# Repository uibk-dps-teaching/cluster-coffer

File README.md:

# Cluster Coffer

See [manual](docs/cluster-coffer.pdf).

See extra fancy [3D PDF](hardware/main-3d.pdf) that works only with Adobe Reader / Acrobat.

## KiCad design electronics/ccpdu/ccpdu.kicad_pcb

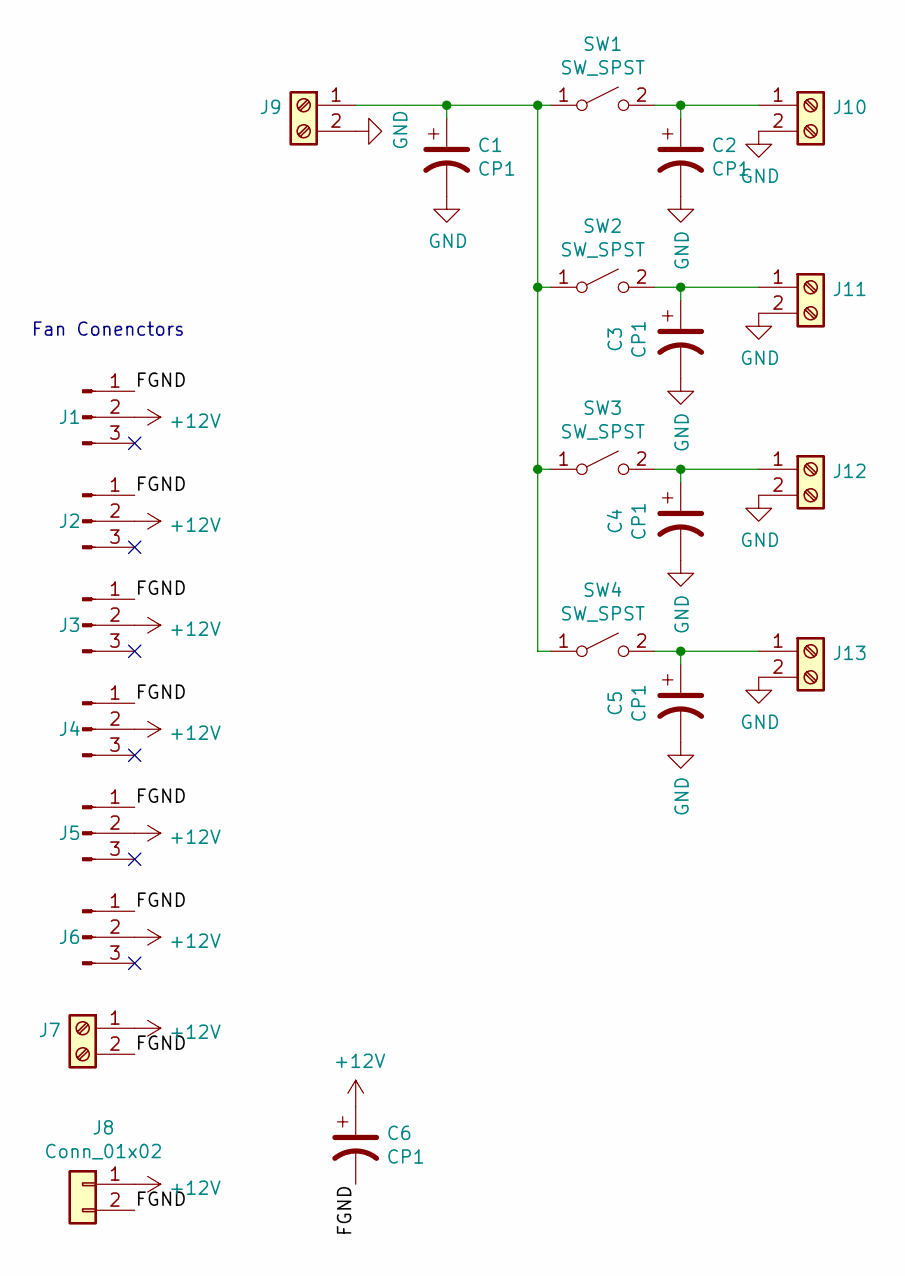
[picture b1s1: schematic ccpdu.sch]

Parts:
C1, C2, C3, C4, C5, C6: CP1; CP_Radial_D5.0mm_P2.50mm; DigikeyPN 493-12902-1-ND
J1, J2, J3, J4, J5, J6: Conn_01x03_Male; Molex_KK-254_AE-6410-03A_1x03_P2.54mm_Vertical; DigikeyPN WM2701-ND
J7, J9, J10, J11, J12, J13: Screw_Terminal_01x02; 284391-2; DigikeyPN A98159-ND
J8: Conn_01x02; HTLCONN_01x02
SW1, SW2, SW3, SW4: SW_SPST; RS-448-0747

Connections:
+12V: C6.1, J1.2, J2.2, J3.2, J4.2, J5.2, J6.2, J7.1, J8.1
/FGND: C6.2, J1.1, J2.1, J3.1, J4.1, J5.1, J6.1, J7.2, J8.2
GND: C1.2, C2.2, C3.2, C4.2, C5.2, J9.2, J10.2, J11.2, J12.2, J13.2
unnamed: C1.1, J9.1, SW1.1 (A), SW2.1 (A), SW3.1 (A), SW4.1 (A)
unnamed: C2.1, J10.1, SW1.2 (B)
unnamed: C3.1, J11.1, SW2.2 (B)
unnamed: C4.1, J12.1, SW3.2 (B)
unnamed: C5.1, J13.1, SW4.2 (B)

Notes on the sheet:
Fan Conenctors

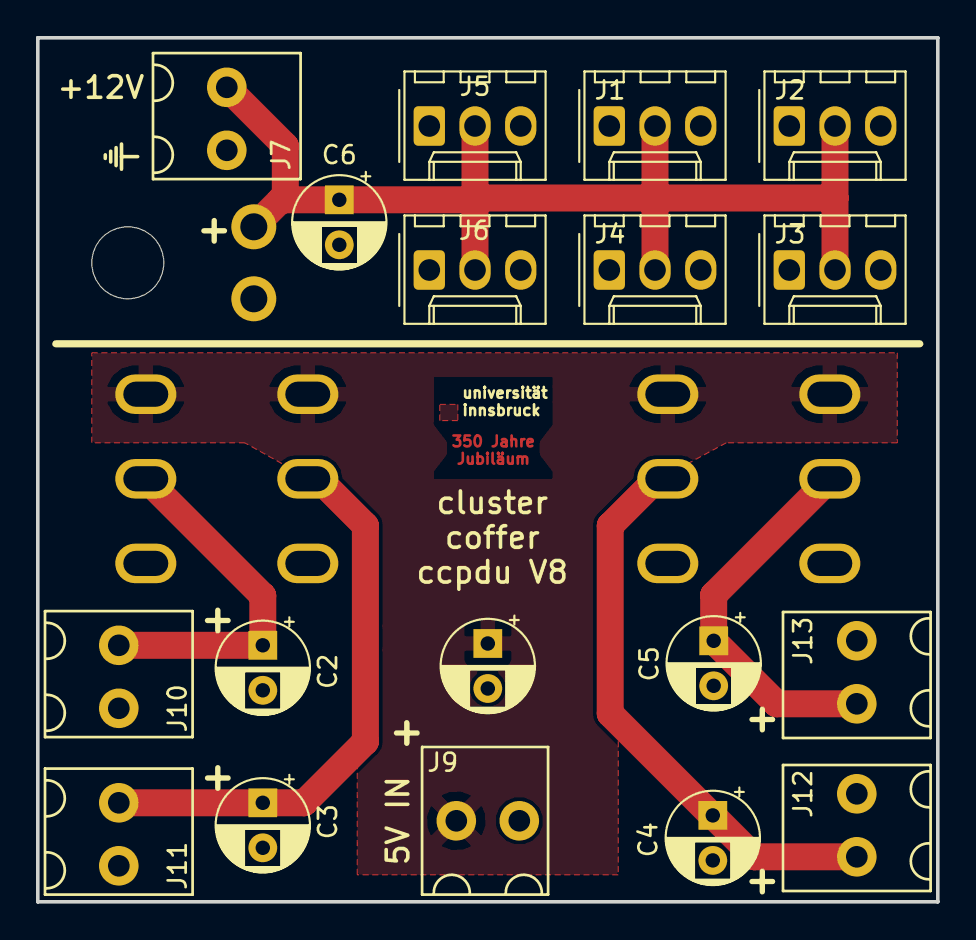
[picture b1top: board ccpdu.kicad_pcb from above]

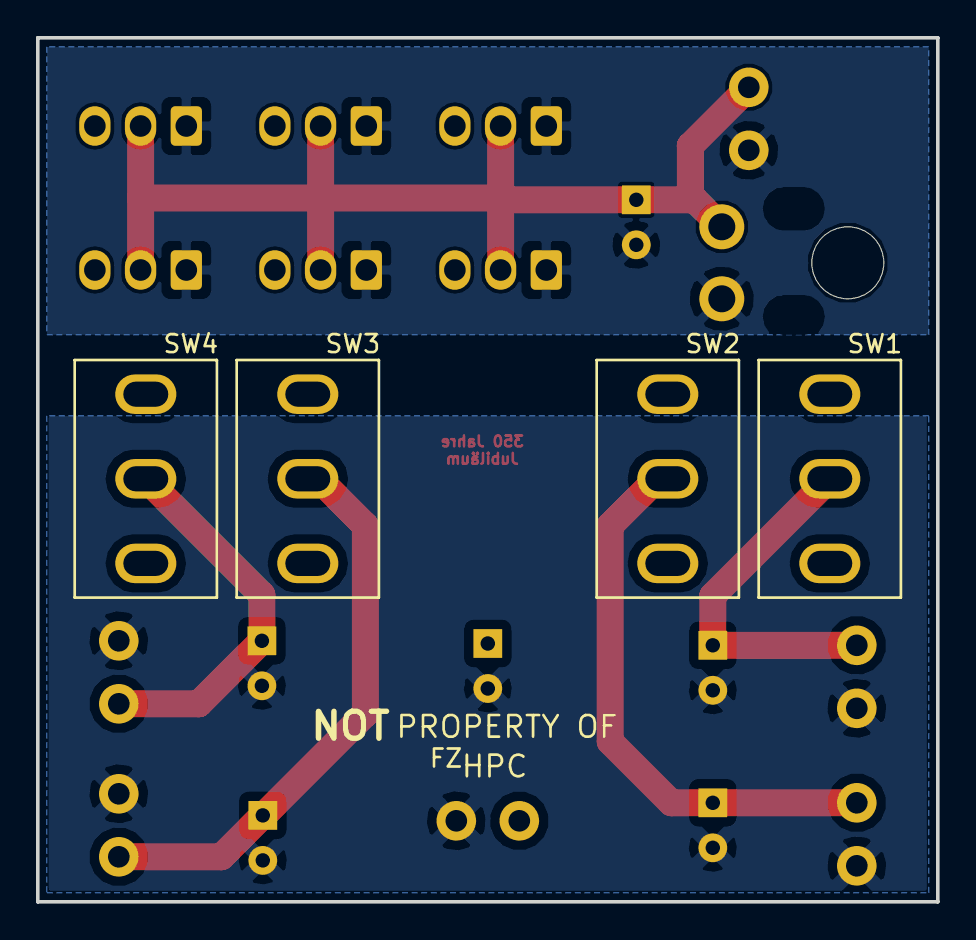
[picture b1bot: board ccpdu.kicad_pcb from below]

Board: 2 copper layers, 50.0 x 48.0 mm, 23 parts (4 on the bottom side), 8 nets.

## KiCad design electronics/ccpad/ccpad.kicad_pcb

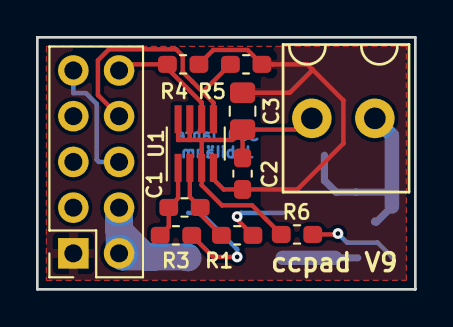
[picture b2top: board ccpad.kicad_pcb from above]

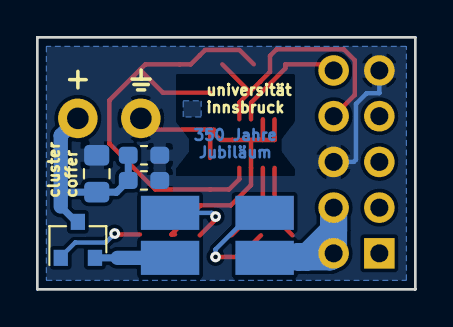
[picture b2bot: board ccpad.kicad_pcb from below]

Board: 2 copper layers, 21.0 x 14.0 mm, 16 parts (5 on the bottom side), 12 nets.

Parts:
C1: C_Small; C_0603_1608Metric_Pad1.05x0.95mm_HandSolder
C2: 470n; C_0603_1608Metric_Pad1.05x0.95mm_HandSolder
C3: 100n; C_0805_2012Metric_Pad1.15x1.40mm_HandSolder
C4, C5: C; C_0603_1608Metric_Pad1.05x0.95mm_HandSolder
C6: C; C_0805_2012Metric_Pad1.15x1.40mm_HandSolder
J1: Conn_02x05_Odd_Even; PinSocket_2x05_P2.54mm_Vertical
J2: Screw_Terminal_01x02; 284391-2
Q1: Q_PMOS_GSD; SOT-23
R1, R3, R4, R5: R; R_0603_1608Metric_Pad1.05x0.95mm_HandSolder
R2: 10m; LVK24
R6: 100k; R_0603_1608Metric_Pad1.05x0.95mm_HandSolder
U1: INA219; SOT-23-8_Handsoldering

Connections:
+5V: C4.1, C5.1, C6.1, J2.1, Q1.3
/M4_3V3: C2.1, C3.1, J1.1, R4.1, R5.1, U1.4
/M4_5V: J1.2, J1.4, R2.1
/M4_I2C3_SCL: J1.8, R5.2, U1.5
/M4_I2C3_SDA: J1.10, R4.2, U1.6
GND: C2.2, C3.2, C4.2, C5.2, C6.2, J1.6, J1.9, J2.2, R6.2, U1.3, U1.7, U1.8
unnamed: C1.1, R1.2, U1.2
unnamed: C1.2, R3.2, U1.1
unnamed: Q1.2, R2.4
unnamed: Q1.1, R6.1
unnamed: R1.1, R2.3
unnamed: R2.2, R3.1

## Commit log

2020-08-14 Init
2020-08-14 README: Add picture
